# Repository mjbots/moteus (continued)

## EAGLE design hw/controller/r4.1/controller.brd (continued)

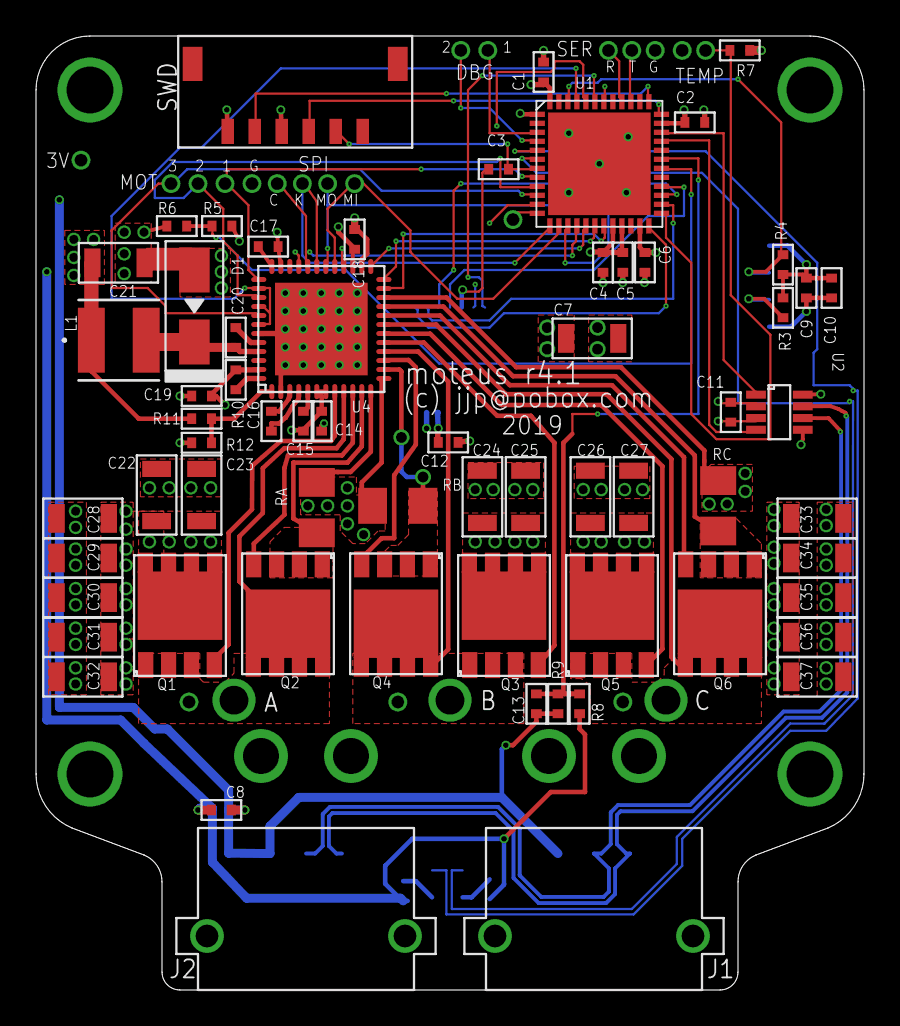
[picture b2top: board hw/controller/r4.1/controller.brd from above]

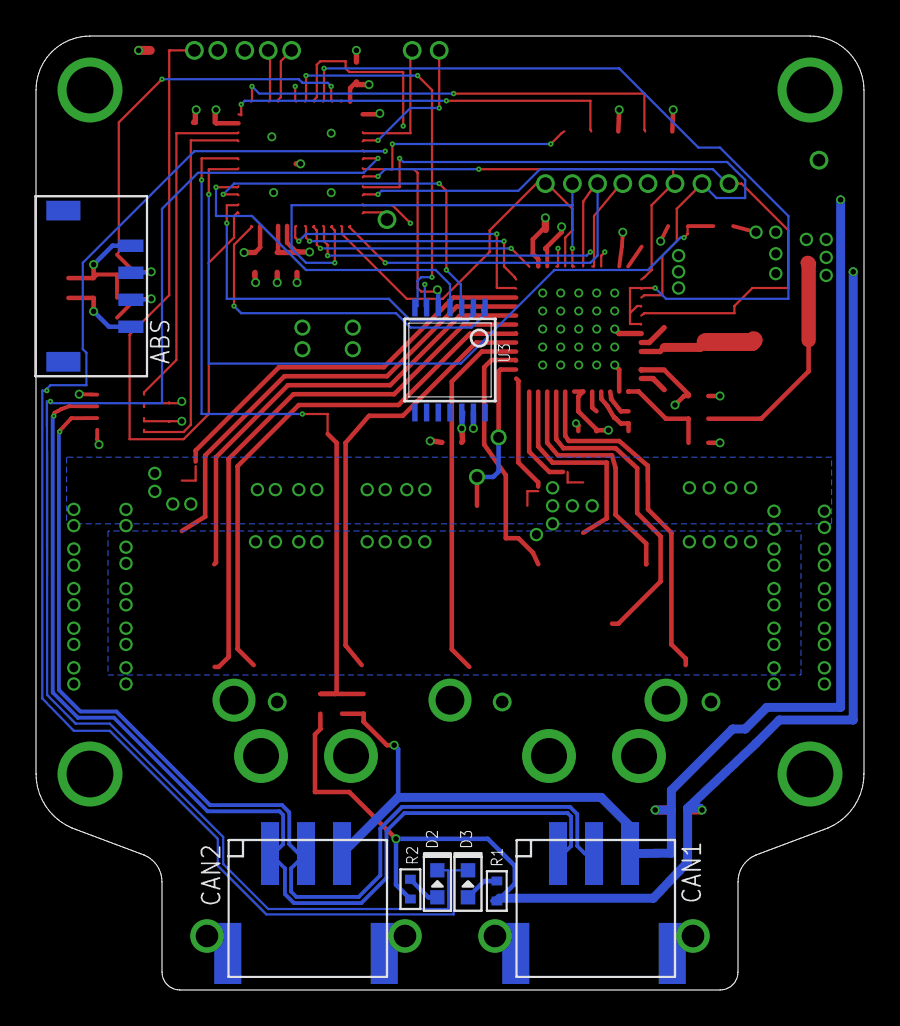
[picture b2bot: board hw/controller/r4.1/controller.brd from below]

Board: 4 copper layers, 46.0 x 53.0 mm, 103 parts (8 on the bottom side), 67 nets.

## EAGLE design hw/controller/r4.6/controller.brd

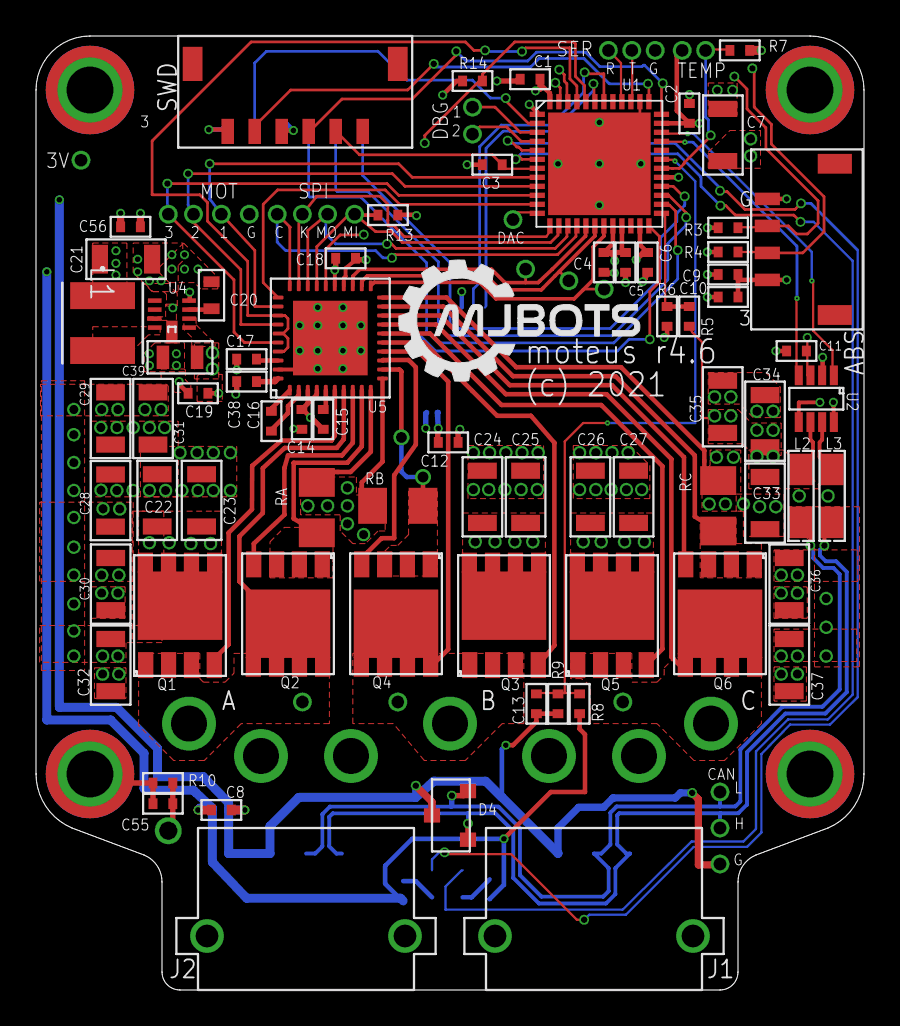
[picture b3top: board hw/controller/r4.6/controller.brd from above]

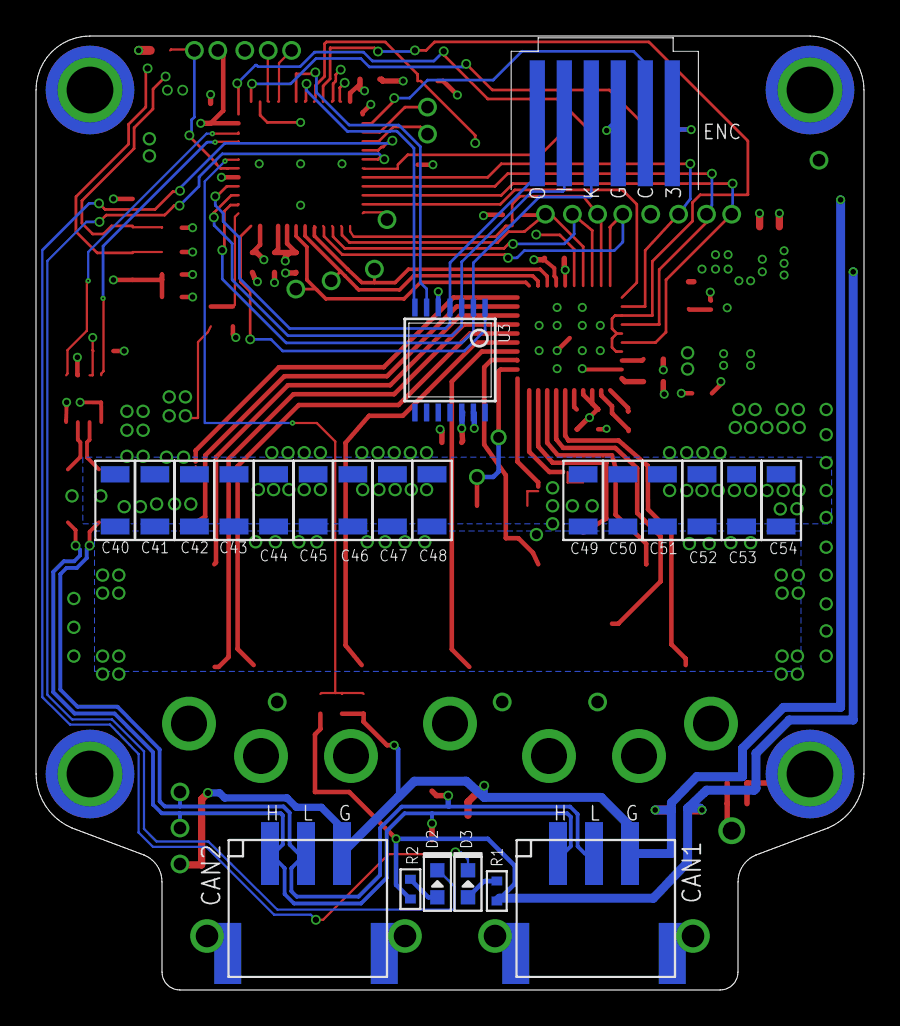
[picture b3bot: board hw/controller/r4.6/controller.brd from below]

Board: 4 copper layers, 46.0 x 53.0 mm, 129 parts (23 on the bottom side), 70 nets.

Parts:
A: PAD16AWG_PAD; 16AWG_PAD
ABS: JST_ZH4; JST_S4B-ZR-SM4A-TF(LF)(SN)
B: PAD16AWG_PAD; 16AWG_PAD
C: PAD16AWG_PAD; 16AWG_PAD
C1, C2, C3, C5, C6, C8, C10, C11, C12, C13, C18: 0.1uF; C0402
C4, C9, C15, C17, C38, C56: 1uF; C0402
C7, C21: 10uF; C1206
C14, C16: 0.1uF 50V; C0402
C19: 0.47uF 50V; C0402
C20: 1uF; C0603
C22, C23, C24, C25, C26, C27, C28, C29, C30, C31, C32, C33, C34, C35, C36, C37: 10uF 50V; C1206
C39: 1uF 100V; C0805
C40, C41, C42, C43, C44, C45, C46, C47, C48, C49, C50, C51, C52, C53, C54: DNP; C1206_NOCREAM
C55: DNP; C0402
CAN1, CAN2: JST-PH3; JST_S3B-PH-SM4-TB(LF)(SN)
CUR1, CUR2, CUR3: PAD24AWG_PAD; 24AWG_PAD
D2, D3: MF-LED-0603-RED; LED0603
D4: DUAL_TVS; SOT23-3
D33: PAD24AWG_PAD; 24AWG_PAD
DA: PAD24AWG_PAD; 24AWG_PAD
DAC: PAD24AWG_PAD; 24AWG_PAD
DB: PAD24AWG_PAD; 24AWG_PAD
DBG1, DBG2: PAD24AWG_PAD; 24AWG_PAD
DC: PAD24AWG_PAD; 24AWG_PAD
DG1, DG2: PAD24AWG_PAD; 24AWG_PAD
DRV_CS: PAD24AWG_PAD; 24AWG_PAD
DRV_MISO: PAD24AWG_PAD; 24AWG_PAD
DRV_MOSI: PAD24AWG_PAD; 24AWG_PAD
DRV_SCK: PAD24AWG_PAD; 24AWG_PAD
DTR: PAD24AWG_PAD; 24AWG_PAD
DTX: PAD24AWG_PAD; 24AWG_PAD
ENC: PICO-SPOX-6NOPASTE; PICO-SPOX-SMT-RA-6-NOPASTE
J1, J2: XT30XT30PW_MALE; XT30PW_MALE
L1: SRN4018-220M; IND_BOURNS_SRN4018
L2, L3: HALF_CHOKE; 1812_COMMON_HALF
M1, M2, M3, M4: MOUNT; M2.5MOUNT
MOT1, MOT2, MOT3: PAD24AWG_PAD; 24AWG_PAD
Q1, Q2, Q3, Q4, Q5, Q6: TPH1R204PLSOP_ADVANCE_8; SOP_ADVANCE_8
R1, R2: 560; R0402
R3, R4, R13, R14: 2k; R0402
R5: 100k 1%; R0402
R6: 4.7k 1%; R0402
R7, R9: 10k 1%; R0402
R8: 47k NTC; R0402
R10: DNP; R0402
RA: 0.5mOhm 1% 2W; M1206
RB: 0.5mOhm 1% 2W; M1206
RC: 0.5mOhm 1% 2W; M1206
SH1, SH2, SH3: SHORTT5; SHORT_TOP-50
SH4: SHORTMEDIUM; SHORT_TOP-MEDIUM
SWD: JST-ZH6; JST_S6B-ZR-SM4A-TF(LF)(SN)
TEMP1, TEMP2: PAD24AWG_PAD; 24AWG_PAD
U1: STM32G474CEU6; QFN50P700X700X60-49N
U2: TCAN334GSOT23; SOT23-8
U3: AS5147; TSSOP14
U4: MAX15062AATA+T; 21-0487A_MXM
U5: DRV8353S; WQFN-40

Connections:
+3V3: ABS.1, C1.P$1, C2.P$1, C4.P$1, C5.P$1, C6.P$1, C7.P$2, C8.P$1, C9.P$1, C10.P$1, C11.P$1, C12.P$1, C18.P$2, C21.P$1, C56.P$1, D33.P$1, ENC.1, L1.1, R1.P$1, R2.P$1, R3.P$1, R4.P$1, R8.P$1, R13.P$1, R14.P$1, SWD.6, TEMP1.P$1, U1.1, U1.20, U1.21, U1.23, U1.35, U1.48, U2.3, U3.12, U4.4, U5.24
AS5047_A: U1.43, U3.7
AS5047_B: U1.42, U3.6
AS5047_CS: U1.24, U3.1
AS5047_MISO: ENC.5, U1.27, U3.3
AS5047_MOSI: ENC.6, U1.28, U3.4
AS5047_SCK: ENC.4, U1.26, U3.2
CAN2_N: L2.P$2, U2.6
CAN2_P: L3.P$2, U2.7
CAN_N: CAN1.2, CAN2.2, D4.2, L2.P$1
CAN_P: CAN1.1, CAN2.1, D4.1, L3.P$1
CAN_RX: U1.33, U2.4
CAN_TX: U1.34, U2.1
CUR1: CUR1.P$1, U1.17, U5.23
CUR2: CUR2.P$1, U1.18, U5.22
CUR3: CUR3.P$1, U1.19, U5.21
DAC: DAC.P$1, U1.12
DEBUG1: DBG1.P$1, U1.3
DEBUG2: DBG2.P$1, U1.4
DEBUG_RX: DTR.P$1, U1.40
DEBUG_TX: DTX.P$1, U1.39
DRV8323_CS: DRV_CS.P$1, U1.16, U5.30
DRV8323_MISO: DRV_MISO.P$1, R13.P$2, U1.14, U5.27
DRV8323_MOSI: DRV_MOSI.P$1, U1.15, U5.28
DRV8323_SCLK: DRV_SCK.P$1, U1.13, U5.29
GHA: Q1.4, U5.6
GHB: Q3.4, U5.15
GHC: Q5.4, U5.16
GLA: Q2.4, U5.8
GLB: Q4.4, U5.13
GLC: Q6.4, U5.18
GND: ABS.4, C1.P$2, C2.P$2, C3.P$2, C4.P$2, C5.P$2, C6.P$2, C7.P$1, C8.P$2, C9.P$2, C10.P$2, C11.P$2, C12.P$2, C13.P$2, C18.P$1, C20.P$2, C21.P$2, C56.P$2, CAN1.3, CAN2.3, D4.3, DG1.P$1, DG2.P$1, ENC.3, R6.P$1, R7.P$2, R9.P$2, SH4.2, SWD.4, U1.29, U1.38, U1.49, U2.2, U2.5, U2.8, U3.5, U3.13, U4.7, U5.25
I2C_ABS_SCL: ABS.2, R4.P$2, U1.46
I2C_ABS_SDA: ABS.3, R3.P$2, U1.47
LED1: D3.CATHODE, U1.5
LED2: D2.CATHODE, U1.6
MOTOR1: MOT1.P$1, U1.8, U5.32
MOTOR2: MOT2.P$1, U1.9, U5.34
MOTOR3: MOT3.P$1, U1.10, U5.36
MOTOR_ENABLE: U1.11, U5.31
MOTOR_FAULT: R14.P$2, U1.44, U5.26
MOTOR_HIZ: U1.45, U5.33, U5.35, U5.37
unnamed: C55.P$1, M3.P$1, R10.P$1
unnamed: C38.P$2, U5.40
unnamed: C20.P$1, U4.3
unnamed: C16.P$2, U5.1
unnamed: C16.P$1, U5.2
unnamed: C15.P$2, U5.5
unnamed: C17.P$2, U5.38
unnamed: D3.ANODE, R1.P$2
unnamed: D2.ANODE, R2.P$2
NRST: C3.P$1, SWD.2, U1.7
SECONDARY_ENC_CS: ENC.2, U1.2
SHA: A.1, DA.P$1, Q1.1, Q1.2, Q1.3, Q2.5, Q2.6, Q2.7, Q2.8, Q2.PAD, U5.7
SHB: B.1, DB.P$1, Q3.1, Q3.2, Q3.3, Q4.5, Q4.6, Q4.7, Q4.8, Q4.PAD, U5.14
SHC: C.1, DC.P$1, Q5.1, Q5.2, Q5.3, Q6.5, Q6.6, Q6.7, Q6.8, Q6.PAD, U5.17
SNA: SH1.1, U5.10
SNB: SH2.1, U5.11
SNC: SH3.1, U5.20
SPA: Q2.1, Q2.2, Q2.3, RA.2, U5.9
SPB: Q4.1, Q4.2, Q4.3, RB.2, U5.12
SPC: Q6.1, Q6.2, Q6.3, RC.2, U5.19
SWCLK: SWD.5, U1.37
SWDIO: SWD.3, U1.36
V+: C14.P$1, C15.P$1, C19.P$1, C22.P$1, C23.P$1, C24.P$1, C25.P$1, C26.P$1, C27.P$1, C28.P$1, C29.P$1, C30.P$1, C31.P$1, C32.P$1, C33.P$1, C34.P$1, C35.P$1, C36.P$1, C37.P$1, C39.P$1, C40.P$1, C41.P$1, C42.P$1, C43.P$1, C44.P$1, C45.P$1, C46.P$1, C47.P$1, C48.P$1, C49.P$1, C50.P$1, C51.P$1, C52.P$1, C53.P$1, C54.P$1, J1.1, J2.1, Q1.5, Q1.6, Q1.7, Q1.8, Q1.PAD, Q3.5, Q3.6, Q3.7, Q3.8, Q3.PAD, Q5.5, Q5.6, Q5.7, Q5.8, Q5.PAD, R5.P$2, U4.1, U4.2, U5.3, U5.4
V-: C14.P$2, C17.P$1, C19.P$2, C22.P$2, C23.P$2, C24.P$2, C25.P$2, C26.P$2, C27.P$2, C28.P$2, C29.P$2, C30.P$2, C31.P$2, C32.P$2, C33.P$2, C34.P$2, C35.P$2, C36.P$2, C37.P$2, C38.P$1, C39.P$2, C40.P$2, C41.P$2, C42.P$2, C43.P$2, C44.P$2, C45.P$2, C46.P$2, C47.P$2, C48.P$2, C49.P$2, C50.P$2, C51.P$2, C52.P$2, C53.P$2, C54.P$2, C55.P$2, J1.2, J2.2, R10.P$2, RA.1, RB.1, RC.1, SH1.2, SH2.2, SH3.2, SH4.1, U5.39, U5.P1, U5.P2, U5.P3, U5.P7, U5.P8, U5.P9, U5.P12, U5.P13, U5.P14, U5.P17, U5.P18, U5.P19, U5.PAD
VBAT_SENSE: R5.P$1, R6.P$2, U1.25
VSW: L1.2, U4.8
VTEMP_FET: C13.P$1, R8.P$2, R9.P$1, U1.31
VTEMP_MOT: R7.P$1, TEMP2.P$1, U1.30

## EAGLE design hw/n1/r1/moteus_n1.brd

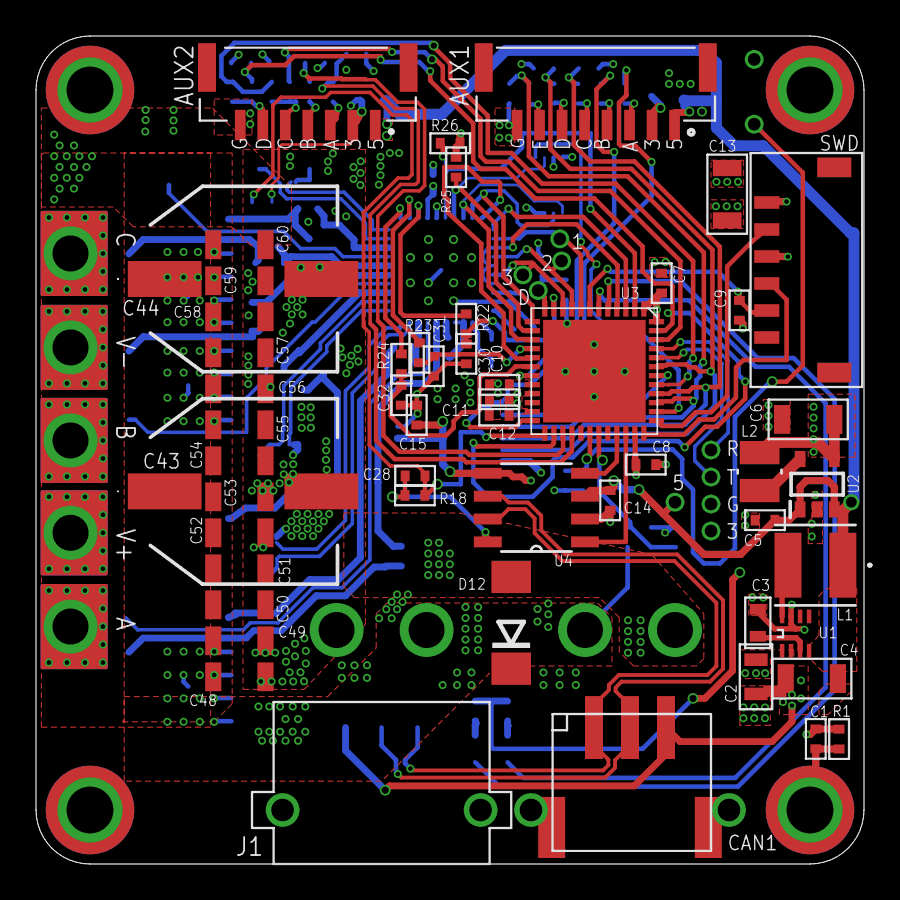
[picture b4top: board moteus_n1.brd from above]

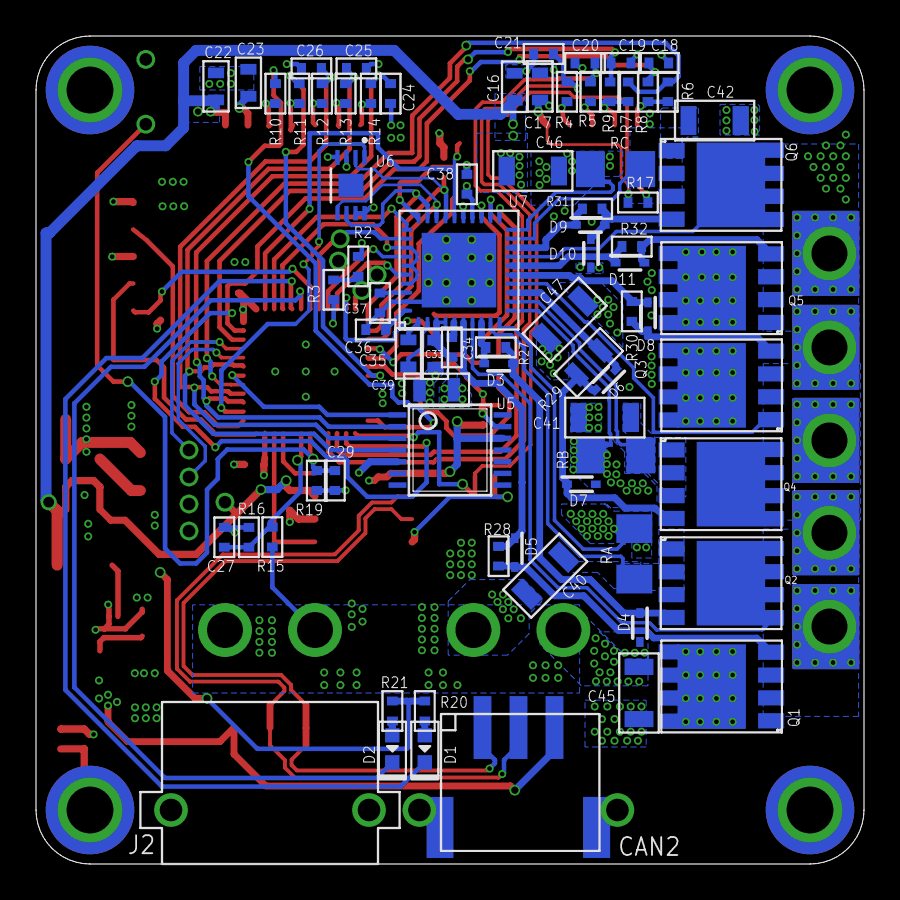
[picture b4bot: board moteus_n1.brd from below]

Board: 4 copper layers, 46.0 x 46.0 mm, 153 parts (82 on the bottom side), 89 nets.

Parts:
A: PAD16AWG_TERM; 16AWG_TERM
AUX1: SM08B-GHS-TB(LF)(SN); JST_SM08B-GHS-TB(LF)(SN)
AUX2: SM07B-GHS-TB(LF)(SN); JST_SM07B-GHS-TB(LF)(SN)
B: PAD16AWG_TERM; 16AWG_TERM
C: PAD16AWG_TERM; 16AWG_TERM
C1, C18, C19, C20, C21, C24, C25, C26: DNP; C0402
C2: 1uF 100V; C0805
C3, C16, C17, C22, C23: 1uF; C0603
C4, C13: 10uF; C1206
C5, C10, C34, C36, C37: 1uF; C0402
C6: 22uF; C1206
C7, C8, C9, C11, C12, C14, C15, C28, C29, C38: 0.1uF; C0402
C27: 0.01uF; C0402
C30, C31, C32: 1000pF; C0402
C33, C35: 0.1uF 100V; C0603
C39: 0.47uF 100V; C0805
C40, C41, C42: 0.1uF 100V; C1206
C43, C44: 100uF 63V; EEHZS1V471UP
C45, C46, C47: 4.7uF 100V; C1206
C48, C49, C50, C51, C52, C53, C54, C55, C56, C57, C58, C59, C60: 4.7uF 100V; C1206_NOCREAM_NOBORDER
CAN1, CAN2: JST-PH3; JST_S3B-PH-SM4-TB(LF)(SN)
D1, D2: MF-LED-0603-RED; LED0603
D3, D4, D5, D6, D7, D8, D9, D10, D11: BAT41KFILM; SODFL1608X70N
D12: DO214AA
D33, D50: PAD24AWG_PAD; 24AWG_PAD
DAC: PAD24AWG_PAD; 24AWG_PAD
DG1: PAD24AWG_PAD; 24AWG_PAD
DTR: PAD24AWG_PAD; 24AWG_PAD
DTX: PAD24AWG_PAD; 24AWG_PAD
J1, J2: XT30XT30PW_MALE; XT30PW_MALE
L1: SRN4018-220M; IND_BOURNS_SRN4018
L2: 74404024100; IND_4024100_WRE
M1, M2, M3, M4: MOUNT; M2.5MOUNT
MOT1, MOT2, MOT3: PAD24AWG_PAD; 24AWG_PAD
Q1, Q3, Q5: TPH1R204PL_VIAS; SOP_ADVANCE_8_VIAS
Q2, Q4, Q6: TPH1R204PLSOP_ADVANCE_8; SOP_ADVANCE_8
R1, R2: DNP; R0402
R3, R15: 100k 1%; R0402
R4, R5, R8, R9, R10, R11, R12, R13, R14: 100; R0402
R6, R7, R25, R26: 2k; R0402
R16: 4.7k 1%; R0402
R17: 47k NTC; R0402
R18, R19: 10k 1%; R0402
R20, R21: 560; R0402
R22, R23, R24: 22; R0402
R27, R28, R30, R31, R32: 7.5; R0402
R29: 7.5; R0805
RA: 0.5mOhm 1% 2W; M1206
RB: 0.5mOhm 1% 2W; M1206
RC: 0.5mOhm 1% 2W; M1206
SH1, SH2, SH3: SHORTT5; SHORT_TOP-50
SH4: SHORTMEDIUM; SHORT_TOP-MEDIUM
SWD: JST-ZH6; JST_S6B-ZR-SM4A-TF(LF)(SN)
TEMP1, TEMP2: PAD24AWG_PAD; 24AWG_PAD
U1: MAX15062AATA+T; 21-0487A_MXM
U2: XC9265A331MR-G; SOT95P280X130-5N
U3: STM32G474CEU6; QFN50P700X700X60-49N
U4: TCAN1042HGV; SOIC8
U5: AS5147; TSSOP14
U6: CAT25080HU4I-GT3UDFN8_2X3_ONS-M; UDFN8_2X3_ONS-M
U7: DRV8353S; WQFN-40
VN: PAD16AWG_TERM; 16AWG_TERM
VP: PAD16AWG_TERM; 16AWG_TERM

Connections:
+3V3: AUX1.2, AUX2.2, C6.P$1, C7.P$1, C8.P$1, C10.P$1, C11.P$1, C12.P$1, C13.P$2, C15.P$1, C17.P$1, C23.P$1, C38.P$2, D33.P$1, L2.1, R2.P$2, R17.P$1, R20.P$1, R21.P$1, R25.P$1, R26.P$1, SWD.6, TEMP1.P$1, U2.4, U3.1, U3.20, U3.21, U3.23, U3.35, U3.48, U4.5, U5.12, U6.3, U6.7, U6.8, U7.24
+5V: AUX1.1, AUX2.1, C4.P$1, C5.P$1, C14.P$1, C16.P$1, C22.P$1, D50.P$1, L1.1, U1.4, U2.1, U2.3, U4.3
AS5047_CS: U3.42, U5.1
AS5047_MISO: C26.P$1, R12.P$2, U3.40, U5.3
AS5047_MOSI: C25.P$1, R13.P$2, U3.43, U5.4
AS5047_SCK: C24.P$1, R14.P$2, U3.39, U5.2
AUX_SC1: C20.P$1, R5.P$2, U3.27
AUX_SC2: C21.P$1, R4.P$2, U3.28
AUX_SCL: C19.P$1, R9.P$2, U3.46
AUX_SDA: C18.P$1, R8.P$2, U3.26, U3.47
CAN_N: CAN1.2, CAN2.2, U4.6
CAN_P: CAN1.1, CAN2.1, U4.7
CAN_RX: U3.33, U4.4
CAN_TX: U3.34, U4.1
CUR1: R22.P$1, U7.23
CUR2: R23.P$1, U7.22
CUR3: R24.P$1, U7.21
DAC: DAC.P$1, R2.P$1, R3.P$2, U3.12
DEBUG_RX: DTR.P$1, U3.45
DEBUG_TX: DTX.P$1, U3.44
DRV8323_CS: U3.17, U7.30
DRV8323_MISO: R25.P$2, U3.14, U6.2, U7.27
DRV8323_MOSI: U3.15, U6.5, U7.28
DRV8323_SCLK: U3.13, U6.6, U7.29
EEPROM_CS: U3.38, U6.1
FCUR1: C30.P$1, R22.P$2, U3.11
FCUR2: C31.P$1, R23.P$2, U3.16
FCUR3: C32.P$1, R24.P$2, U3.18
GHA: D5.1, R28.P$1, U7.6
GHA_D: D5.2, Q1.4, R28.P$2
GHB: D8.1, R30.P$1, U7.15
GHB_D: D8.2, Q3.4, R30.P$2
GHC: D11.1, R32.P$1, U7.16
GHC_D: D11.2, Q5.4, R32.P$2
GLA: D3.1, R27.P$1, U7.8
GLA_D: D3.2, D4.1, Q2.4, R27.P$2
GLB: D6.1, R29.P$1, U7.13
GLB_D: D6.2, D7.1, Q4.4, R29.P$2
GLC: D9.1, R31.P$1, U7.18
GLC_D: D9.2, D10.1, Q6.4, R31.P$2
GND: AUX1.8, AUX2.7, C3.P$2, C4.P$2, C5.P$2, C6.P$2, C7.P$2, C8.P$2, C9.P$2, C10.P$2, C11.P$2, C12.P$2, C13.P$1, C14.P$2, C15.P$2, C16.P$2, C17.P$2, C18.P$2, C19.P$2, C20.P$2, C21.P$2, C22.P$2, C23.P$2, C24.P$2, C25.P$2, C26.P$2, C27.P$2, C28.P$2, C29.P$2, C30.P$2, C31.P$2, C32.P$2, C38.P$1, CAN1.3, CAN2.3, DG1.P$1, R3.P$1, R16.P$1, R18.P$2, R19.P$2, SH4.2, SWD.4, U1.7, U2.2, U3.49, U4.2, U4.8, U5.5, U5.13, U6.4, U7.25
I2C_PULLUP: R6.P$1, R7.P$1, U3.41
LED1: D1.CATHODE, U3.5
LED2: D2.CATHODE, U3.6
MOTOR1: MOT1.P$1, U3.8, U7.32
MOTOR2: MOT2.P$1, U3.9, U7.34
MOTOR3: MOT3.P$1, U3.10, U7.36
MOTOR_ENABLE: U3.3, U7.31
MOTOR_FAULT: R26.P$2, U3.2, U7.26
MOTOR_HIZ: U3.4, U7.33, U7.35, U7.37
unnamed: C1.P$1, M3.P$1, R1.P$1
unnamed: C36.P$2, U7.40
unnamed: AUX2.3, R4.P$1
unnamed: C3.P$1, U1.3
unnamed: L2.2, U2.5
unnamed: AUX2.4, R5.P$1
unnamed: AUX2.6, R6.P$2, R8.P$1
unnamed: AUX2.5, R7.P$2, R9.P$1
unnamed: AUX1.3, R10.P$1
unnamed: C35.P$2, U7.1
unnamed: AUX1.4, R11.P$1
unnamed: AUX1.5, R12.P$1
unnamed: C35.P$1, U7.2
unnamed: C34.P$2, U7.5
unnamed: AUX1.6, R13.P$1
unnamed: C37.P$2, U7.38
unnamed: D1.ANODE, R20.P$2
unnamed: D2.ANODE, R21.P$2
unnamed: AUX1.7, R14.P$1
NRST: C9.P$1, SWD.2, U3.7
PRIMARY_CS: R11.P$2, U3.19
PRIMARY_EXTRA: R10.P$2, U3.24
SHA: A.1, A.2, A.3, A.4, A.5, A.6, A.7, A.8, A.9, A.10, A.11, A.12, Q1.1, Q1.2, Q1.3, Q2.5, Q2.6, Q2.7, Q2.8, Q2.PAD, U7.7
SHB: B.1, B.2, B.3, B.4, B.5, B.6, B.7, B.8, B.9, B.10, B.11, B.12, Q3.1, Q3.2, Q3.3, Q4.5, Q4.6, Q4.7, Q4.8, Q4.PAD, U7.14
SHC: C.1, C.2, C.3, C.4, C.5, C.6, C.7, C.8, C.9, C.10, C.11, C.12, Q5.1, Q5.2, Q5.3, Q6.5, Q6.6, Q6.7, Q6.8, Q6.PAD, U7.17
SWCLK: SWD.5, U3.37
SWDIO: SWD.3, U3.36
SXA_N: SH1.1, U7.10
SXA_P: C40.P$2, Q2.1, Q2.2, Q2.3, RA.2, U7.9
SXB_N: SH2.1, U7.11
SXB_P: C41.P$2, Q4.1, Q4.2, Q4.3, RB.2, U7.12
SXC_N: SH3.1, U7.20
SXC_P: C42.P$2, Q6.1, Q6.2, Q6.3, RC.2, U7.19
V+: C2.P$1, C33.P$1, C34.P$1, C39.P$1, C40.P$1, C41.P$1, C42.P$1, C43.1, C44.1, C45.P$1, C46.P$1, C47.P$1, C48.P$1, C49.P$1, C50.P$1, C51.P$1, C52.P$1, C53.P$1, C54.P$1, C55.P$1, C56.P$1, C57.P$1, C58.P$1, C59.P$1, C60.P$1, D12.C, J1.1, J2.1, Q1.5, Q1.6, Q1.7, Q1.8, Q1.PAD, Q3.5, Q3.6, Q3.7, Q3.8, Q3.PAD, Q5.5, Q5.6, Q5.7, Q5.8, Q5.PAD, R15.P$2, U1.1, U1.2, U7.3, U7.4, VP.1, VP.2, VP.3, VP.4, VP.5, VP.6, VP.7, VP.8, VP.9, VP.10, VP.11, VP.12
V-: C1.P$2, C2.P$2, C33.P$2, C36.P$1, C37.P$1, C39.P$2, C43.2, C44.2, C45.P$2, C46.P$2, C47.P$2, C48.P$2, C49.P$2, C50.P$2, C51.P$2, C52.P$2, C53.P$2, C54.P$2, C55.P$2, C56.P$2, C57.P$2, C58.P$2, C59.P$2, C60.P$2, D4.2, D7.2, D10.2, D12.A, J1.2, J2.2, R1.P$2, RA.1, RB.1, RC.1, SH1.2, SH2.2, SH3.2, SH4.1, U7.39, U7.P1, U7.P2, U7.P3, U7.P7, U7.P8, U7.P9, U7.P12, U7.P13, U7.P14, U7.P17, U7.P18, U7.P19, U7.PAD, VN.1, VN.2, VN.3, VN.4, VN.5, VN.6, VN.7, VN.8, VN.9, VN.10, VN.11, VN.12
VBAT_SENSE: C27.P$1, R15.P$1, R16.P$2, U3.31
VSW: L1.2, U1.8
VTEMP_FET: C28.P$1, R17.P$2, R18.P$1, U3.25
VTEMP_MOT: C29.P$1, R19.P$1, TEMP2.P$1, U3.30
